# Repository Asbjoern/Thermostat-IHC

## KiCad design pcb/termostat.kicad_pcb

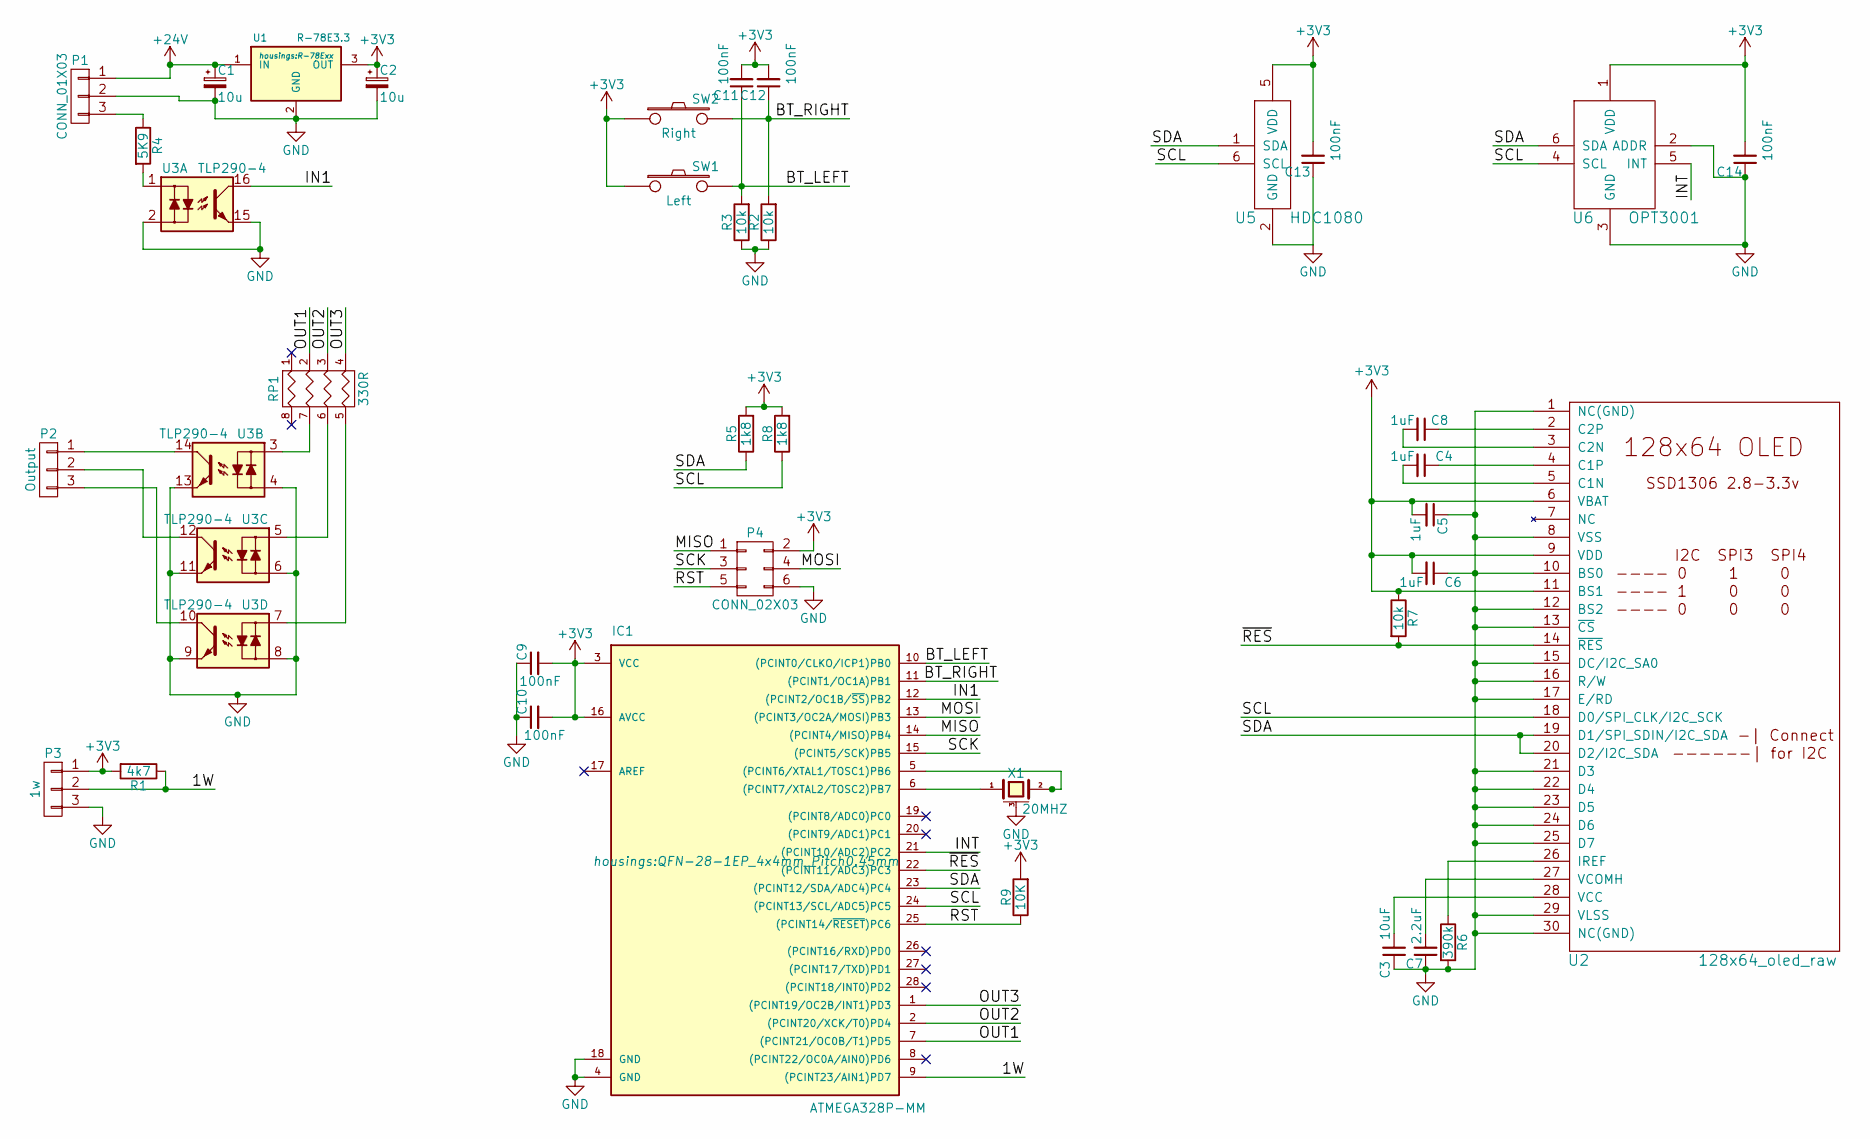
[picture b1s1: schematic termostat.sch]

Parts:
C1: 10u; C_0805
C2: 10u; C_0603
C3: 10uF; C_0805
C4, C5, C6, C8: 1uF; C_0603
C7: 2.2uF; C_0603
C9, C10, C11, C12, C13, C14: 100nF; C_0603
IC1: ATMEGA328P-MM; QFN-28-1EP_4x4mm_Pitch0.45mm
P1: CONN_01X03; TerminalBlock_Pheonix_MPT-2.54mm_3pol
P2: Output; TerminalBlock_Pheonix_MPT-2.54mm_3pol
P3: 1w; TerminalBlock_Pheonix_MPT-2.54mm_3pol
P4: CONN_02X03; pin_2x6_smd
R1: 4k7; R_0603
R2, R3, R7: 10k; R_0603
R4: 5K9; R_0603
R5, R8: 1k8; R_0603
R6: 390k; R_0603
R9: 10K; R_0603
RP1: 330R; R_Array_Convex_4x0603
SW1: Left; SW_SPST_B3S-1000
SW2: Right; SW_SPST_B3S-1000
U1: R-78E3.3; R-78Exx
U2: 128x64_oled_raw; 128x64_oled_raw_bend_same_side
U3: TLP290-4; SOP-16_4.4x10.4mm_Pitch1.27mm
U5: HDC1080; PWSON6
U6: OPT3001; USON6
X1: 20MHZ; CSTCE_V

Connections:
+3V3: C2.1, C5.2, C6.2, C9.2, C10.2, C11.2, C12.2, C13.2, C14.2, IC1.3 (VCC), IC1.16 (AVCC), P3.1, P4.2, R1.2, R5.2, R7.1, R8.2, R9.2, SW1.1, SW2.1, U1.3 (OUT), U2.6 (VBAT), U2.9 (VDD), U2.11 (BS1), U5.5 (VDD), U6.1 (VDD)
+24V: C1.1, P1.1, U1.1 (IN)
/1W: IC1.9 ((PCINT23/AIN1)PD7), P3.2, R1.1
/BT_LEFT: C11.1, IC1.10 ((PCINT0/CLKO/ICP1)PB0), R3.2, SW1.2
/BT_RIGHT: C12.1, IC1.11 ((PCINT1/OC1A)PB1), R2.2, SW2.2
/IN1: IC1.12 ((PCINT2/OC1B/~SS~)PB2), U3.16
/INT: IC1.21 ((PCINT10/ADC2)PC2), U6.5 (INT)
/MISO: IC1.14 ((PCINT4/MISO)PB4), P4.1
/MOSI: IC1.13 ((PCINT3/OC2A/MOSI)PB3), P4.4
/OUT1: IC1.7 ((PCINT21/OC0B/T1)PD5), RP1.2
/OUT2: IC1.2 ((PCINT20/XCK/T0)PD4), RP1.3
/OUT3: IC1.1 ((PCINT19/OC2B/INT1)PD3), RP1.4
/RST: IC1.25 ((PCINT14/~RESET~)PC6), P4.5, R9.1
/SCK: IC1.15 ((PCINT5/SCK)PB5), P4.3
/SCL: IC1.24 ((PCINT13/SCL/ADC5)PC5), R8.1, U2.18 (D0/SPI_CLK/I2C_SCK), U5.6 (SCL), U6.4 (SCL)
/SDA: IC1.23 ((PCINT12/SDA/ADC4)PC4), R5.1, U2.19 (D1/SPI_SDIN/I2C_SDA), U2.20 (D2/I2C_SDA), U5.1 (SDA), U6.6 (SDA)
/~RES: IC1.22 ((PCINT11/ADC3)PC3), R7.2, U2.14 (~RES)
GND: C1.2, C2.2, C3.1, C5.1, C6.1, C7.1, C9.1, C10.1, C13.1, C14.1, IC1.4 (GND), IC1.18 (GND), P1.2, P3.3, P4.6, R2.1, R3.1, R6.2, U1.2 (GND), U2.1 (NC(GND)), U2.8 (VSS), U2.10 (BS0), U2.12 (BS2), U2.13 (~CS), U2.15 (DC/I2C_SA0), U2.16 (R/W), U2.17 (E/RD), U2.21 (D3), U2.22 (D4), U2.23 (D5), U2.24 (D6), U2.25 (D7), U2.29 (VLSS), U2.30 (NC(GND)), U3.2, U3.4, U3.6, U3.8, U3.9, U3.11, U3.13, U3.15, U5.2 (GND), U6.2 (ADDR), U6.3 (GND), X1.3 (case)
unnamed: C3.2, U2.28 (VCC)
unnamed: C4.1, U2.4 (C1P)
unnamed: C4.2, U2.5 (C1N)
unnamed: C7.2, U2.27 (VCOMH)
unnamed: C8.1, U2.2 (C2P)
unnamed: C8.2, U2.3 (C2N)
unnamed: IC1.5 ((PCINT6/XTAL1/TOSC1)PB6), X1.2
unnamed: IC1.6 ((PCINT7/XTAL2/TOSC2)PB7), X1.1
unnamed: P1.3, R4.1
unnamed: P2.1, U3.14
unnamed: P2.2, U3.12
unnamed: P2.3, U3.10
unnamed: R4.2, U3.1
unnamed: R6.1, U2.26 (IREF)
unnamed: RP1.5 (R4), U3.7
unnamed: RP1.6 (R3), U3.5
unnamed: RP1.7 (R2), U3.3

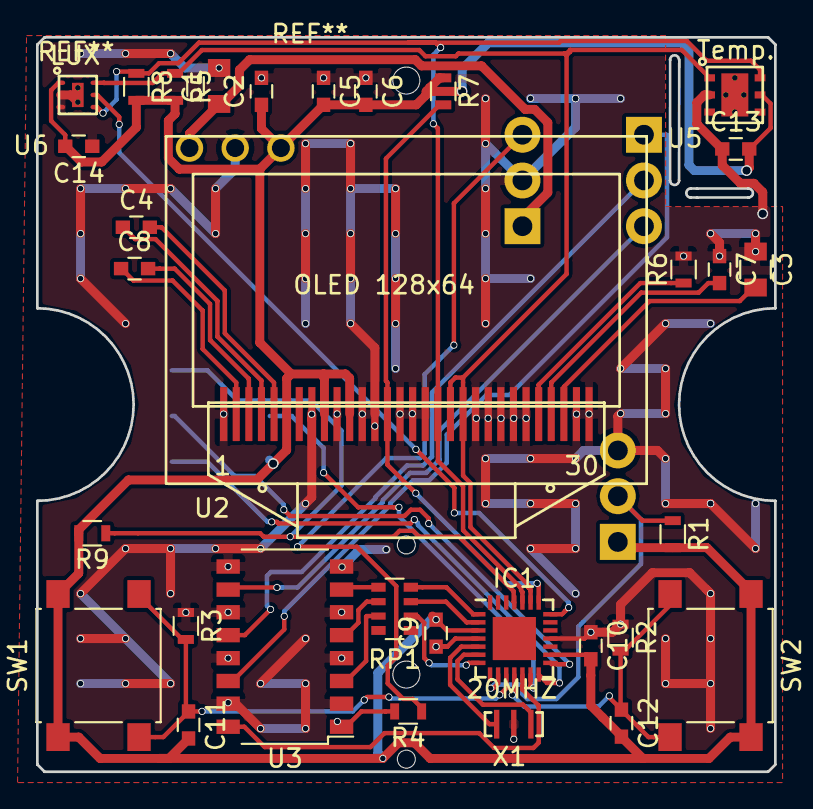
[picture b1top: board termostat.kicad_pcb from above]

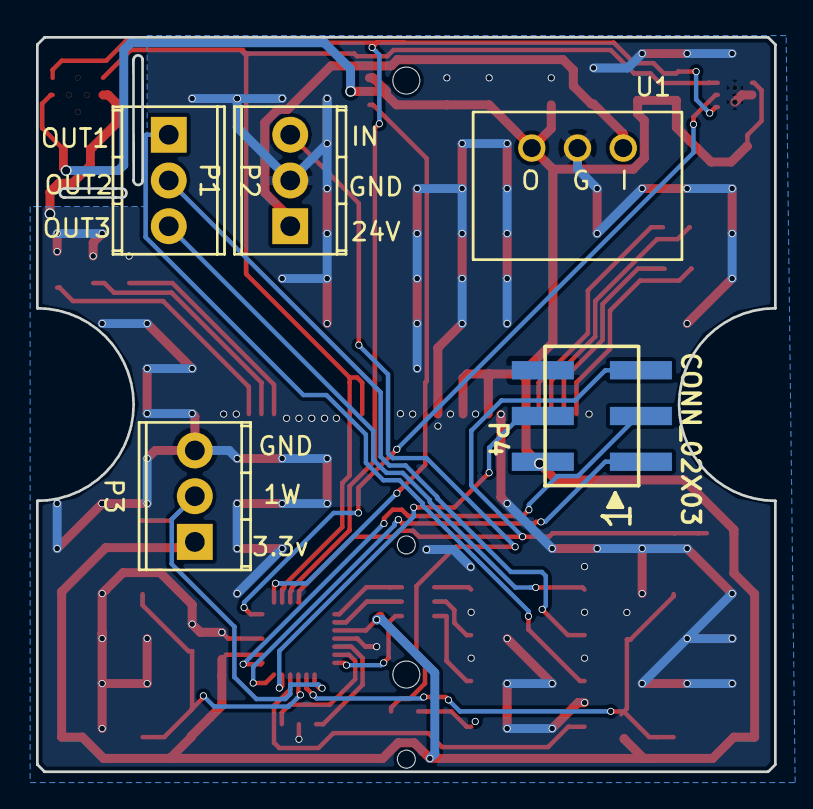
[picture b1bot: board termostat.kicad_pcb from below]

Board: 2 copper layers, 41.0 x 40.8 mm, 37 parts (5 on the bottom side), 35 nets.

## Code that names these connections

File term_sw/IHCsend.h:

#ifndef _ihcsend_h
#define _ihcsend_h
#include "sensordata.h"

#define OUT1 5
#define OUT2 4
#define OUT3 3


static uint8_t outdata[3][9];
static int bitpos;
static unsigned long starttime;

static int val1[3]; //rum x10 / rum x10 / rum x10
static int val2[3]; //setpunkt x10 / ?? / rh x10
static int val3[3]; //gulv x10 / lux / dugpunkt x10

static void IHCfillBuffer();
static void IHCAddBits(int ch, word value, int bits = 12);

void IHCinit();
static void IHCTick(void);

void IHCsetData(Sensordata &data);
	
#endif

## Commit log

2019-01-17 Initial upload of schematic and src
2019-01-19 Data to IHC working
2019-01-19 Added gerber files
2019-01-21 IHC sender now supports negative temperatures
2019-01-21 V1.0 Setpoint receiver added.
2019-01-30 V1.1 Do not busy-wait for ds18b20
